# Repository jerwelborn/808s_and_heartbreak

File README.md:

# bucket-banging

Documentation is available at <http://fab.cba.mit.edu/classes/863.17/Harvard/people/jeremywelborn/>.

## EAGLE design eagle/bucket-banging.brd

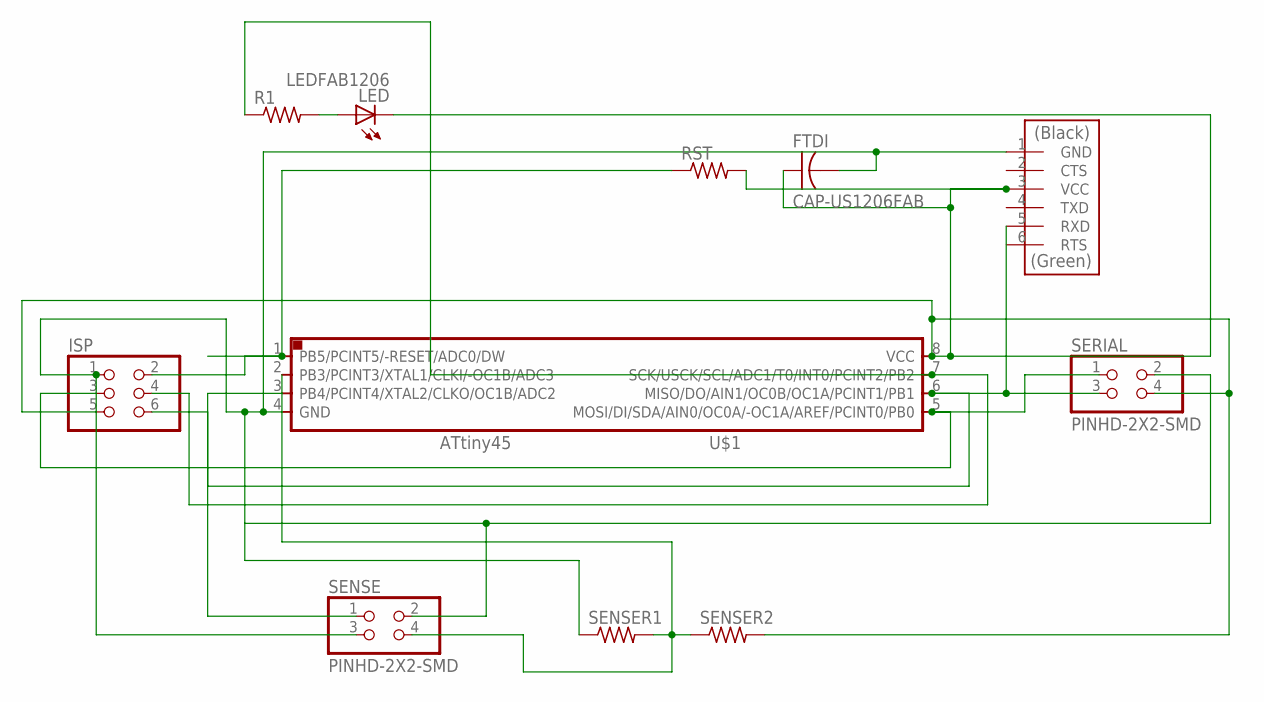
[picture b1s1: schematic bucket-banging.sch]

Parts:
FTDI: CAP-US1206FAB; C1206FAB
ISP: PINHD-2X3-SMD; 2X03SMD
LED: LEDFAB1206; LED1206FAB
R1: RES-US1206FAB; R1206FAB
RST: RES-US1206FAB; R1206FAB
SENSE: PINHD-2X2-SMD; 2X02SMD
SENSER1, SENSER2: RES-US1206FAB; R1206FAB
SERIAL: PINHD-2X2-SMD; 2X02SMD
U$1: ATTINY45SI; SOIC8
U$2: FTDI-SMD-HEADER; 1X06SMD

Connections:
unnamed: FTDI.2, ISP.1, SENSE.2, SENSE.3, SENSER1.1, SERIAL.2, U$1.4 (GND), U$2.1 (GND)
unnamed: ISP.3, SERIAL.1, U$1.5 (MOSI/DI/SDA/AIN0/OC0A/-OC1A/AREF/PCINT0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)
unnamed: ISP.6, SERIAL.3, U$1.6 (MISO/DO/AIN1/OC0B/OC1A/PCINT1/PB1), U$2.5 (RXD)
unnamed: ISP.4, R1.1, U$1.7 (SCK/USCK/SCL/ADC1/T0/INT0/PCINT2/PB2)
unnamed: ISP.2, RST.1, U$1.1 (PB5/PCINT5/-RESET/ADC0/DW)
unnamed: LED.1 (A), R1.2
unnamed: SENSE.4, SENSER1.2, SENSER2.1, U$1.2 (PB3/PCINT3/XTAL1/CLKI/-OC1B/ADC3)
unnamed: FTDI.1, ISP.5, LED.2 (C), RST.2, SENSER2.2, SERIAL.4, U$1.8 (VCC), U$2.3 (VCC)
unnamed: SENSE.1, U$1.3 (PB4/PCINT4/XTAL2/CLKO/OC1B/ADC2)

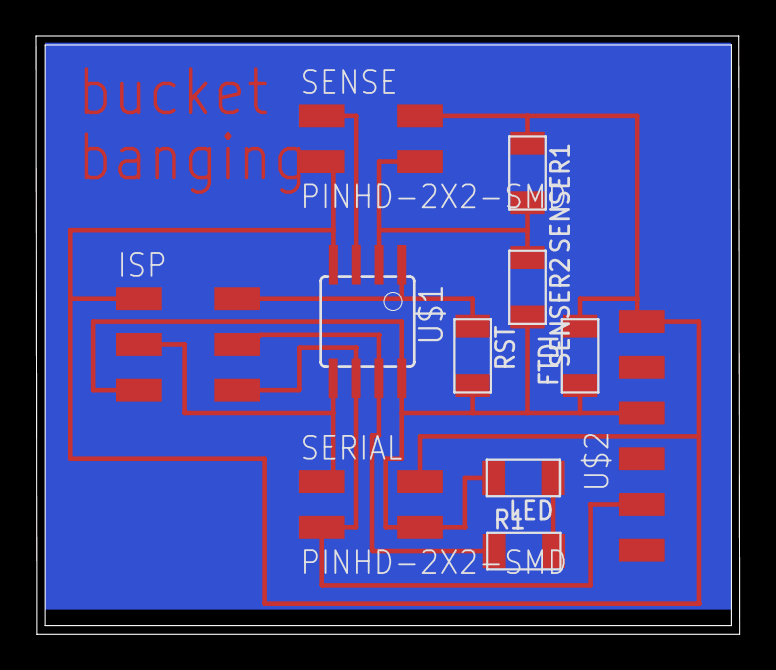
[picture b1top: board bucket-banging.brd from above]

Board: 2 copper layers, 39.1 x 33.2 mm, 11 parts (0 on the bottom side), 9 nets.

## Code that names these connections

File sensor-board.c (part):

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
   pinout:
                          |-------|
                 RST/PB5 -| 1   8 |- VCC
   Rx step sensor -- PB3 -| 2   7 |- PB2/SCK   -- driving debugging LED 
   Tx step sensor -- PB4 -| 3   6 |- PB1/MISO  -- Rx on serial bus, also for FTDI interface
                     GND -| 4   5 |- PB0/MOSI  -- Tx on serial bus
                          |-------|

   --------------------------------------------------------------------------------
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/* def for diode */
#define led_port PORTB
#define led_data_direction DDRB
#define led_pin (1 << PB2)

/* defs for serial bus */
// serial_in_pin i.e. Tx    ASK WHY IN IS TX AND OUT IS RX? IS IT W.R.T. THE BUS?
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#define serial_direction DDRB
#define serial_out_register PORTB // Neil calls this serial_port 
#define serial_in_register PINB  // Neil calls this serial_pins, which is misleading to me 
#define serial_out_pin (1 << PB1) 
#define serial_in_pin (1 << PB0)


/* defs for sensor */
// don't have to touch PB3 this is used by ADC 
#define sensor_tx_port PORTB
#define sensor_tx_direction DDRB
#define sensor_tx_pin (1 << PB4) 


/*
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   CLKPR = (0 << CLKPS3) | (0 << CLKPS2) | (0 << CLKPS1) | (0 << CLKPS0);
   
   // initialize pins / ports
   set(serial_out_register, serial_out_pin); // write 1 to PB2 
   input(serial_direction, serial_out_pin); // PB2 should be listening on bus
   
   clear(sensor_tx_port, sensor_tx_pin); // write 0 to PB4
   output(sensor_tx_direction, sensor_tx_pin); // PB4 is output pin
   
   set(led_port, led_pin);
   output(led_data_direction, led_pin);
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void adc_setup() {
   ADMUX = (0 << REFS2) | (0 << REFS1) | (0 << REFS0) // Vcc ref
      | (0 << ADLAR) // right adjust
      | (0 << MUX3) | (0 << MUX2) | (1 << MUX1) | (1 << MUX0); // PB3
   ADCSRA = (1 << ADEN) // enable
      | (1 << ADPS2) | (1 << ADPS1) | (1 << ADPS0); // prescaler /128
   
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
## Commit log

2017-12-15 setting up remote repo
2017-12-15 adding a lot
2017-12-15 adding a lot again
2017-12-15 added TODOs to wrap up the electronics
2017-12-15 commit before re-writing rpi script
2017-12-16 redesigned to run a record / loop recording drum machine, encapsulated everything in a single for right now, still a lot can be done in software but running with this
